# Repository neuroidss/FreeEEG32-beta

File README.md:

# FreeEEG32-beta

### FreeEEG32 Beta, launching soon on [Crowd Supply](https://www.crowdsupply.com/neuroidss/freeeeg32)!

### Setup

Docker container setup (Linux). Extract the following and run:
- Compilation: `./gcc-arm-none-eabi_run.sh`
- Flashing: `sudo ./openocd_flash.sh`

[Flashing via AC6 with STM32 Blue Pill](https://github.com/neuroidss/FreeEEG32-beta/blob/master/SetupGuides/FreeEEG32_Flashing_via_AC6_w_STM32F103_BluePill.md)

The AC6 stuff is deprecated but the blue pill is still needed.

[OpenVIBE Setup](https://github.com/neuroidss/FreeEEG32-beta/blob/master/SetupGuides/FreeEEG32_OpenVibe_Docker_Readme.md)

### Production files
Gerber:   https://github.com/neuroidss/FreeEEG32-beta/blob/master/AssemblyFiles/KiCAD/out/gerber.zip

Assembly: https://github.com/neuroidss/FreeEEG32-beta/blob/master/AssemblyFiles/KiCAD/out/assembly.zip

BOM:      https://github.com/neuroidss/FreeEEG32-beta/blob/master/AssemblyFiles/bom/components%20FreeEEG32%20beta.csv

PCB fabrication constraints:
* Dims: 70mm x 70mm
* Layers: 4
* Thickness: 1.6mm (can vary, thicker = sturdier)
* Surface finish: HASL Lead free or ENIG (more expensive)
* Material: FR4

Assembly constraints:
* Unique parts: 33 (27 without pin headers)
* SMT Pads:  169
* Thruhole: 23 (pin headers only)
* Assembly sides: both

This project is being launched with the help of [HEG Alpha](hegalpha.com) to make science more accessible.
Custom 2 channel and 19 channel headsets are available by Bernard Markus.

### More

Neuroidss home: https://neuroidss.com

[Alpha 1.5 repo with more content and tests](https://github.com/neuroidss/FreeEEG32-alpha1.5)

[BrainFlow support](https://brainflow.readthedocs.io/en/stable/)

[Webapp (WIP)](https://github.com/moothyknight/eegpwa)

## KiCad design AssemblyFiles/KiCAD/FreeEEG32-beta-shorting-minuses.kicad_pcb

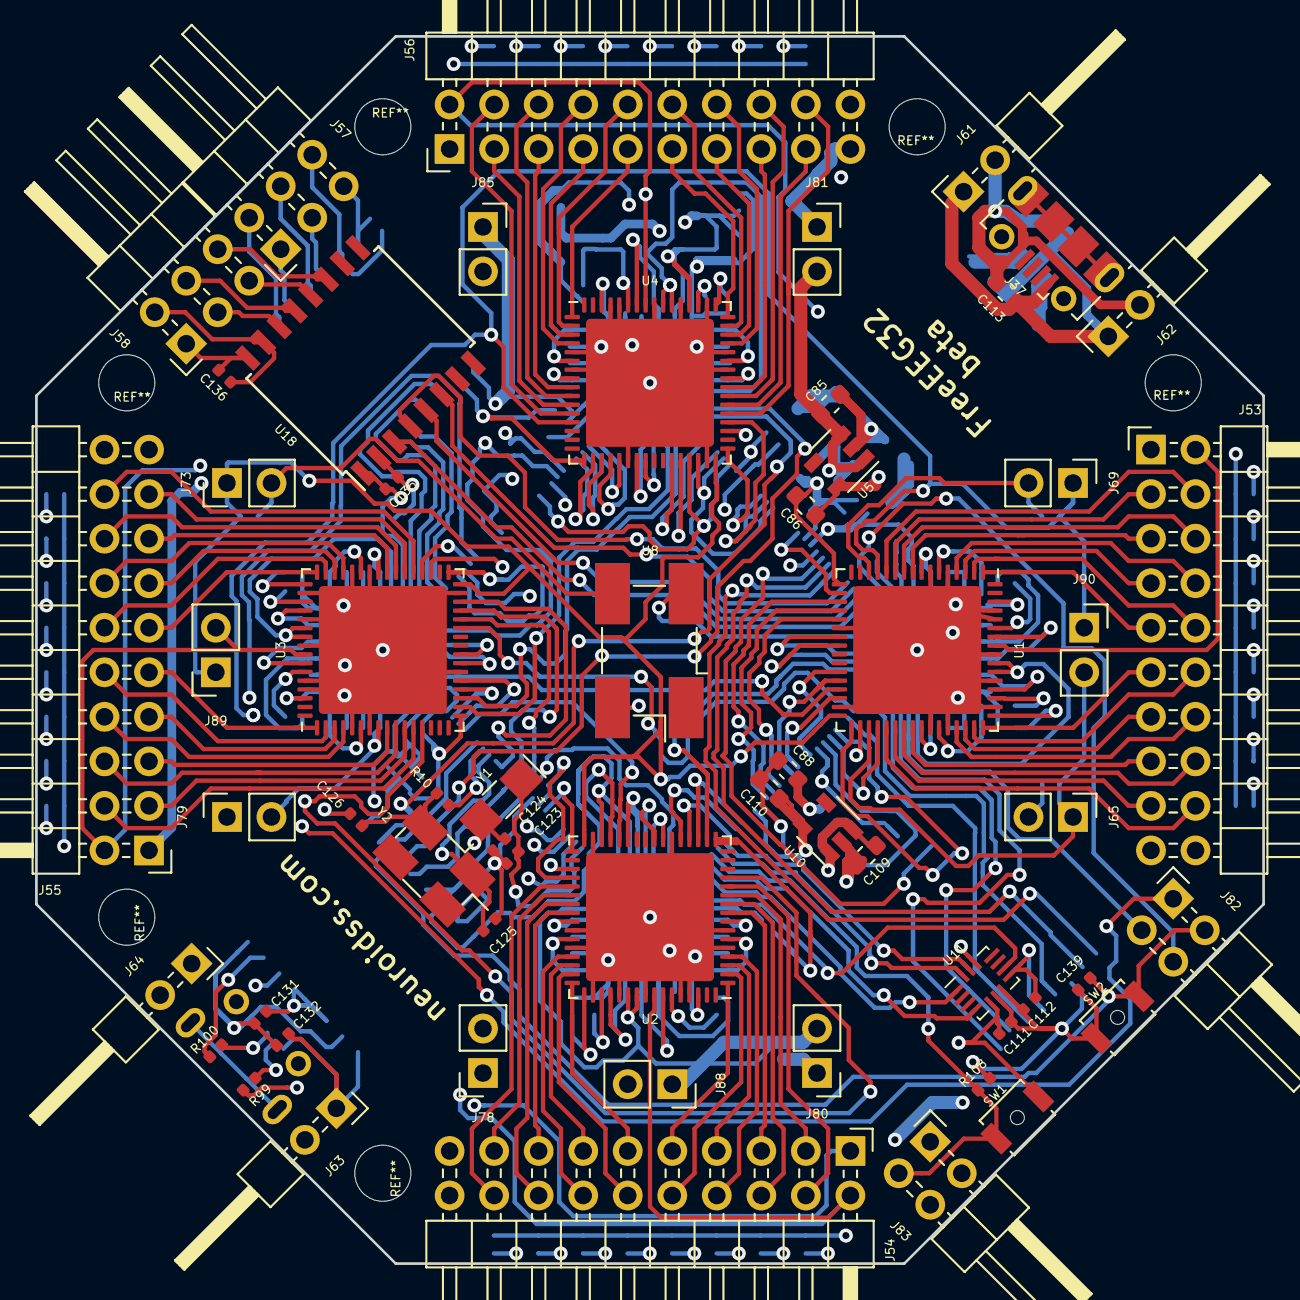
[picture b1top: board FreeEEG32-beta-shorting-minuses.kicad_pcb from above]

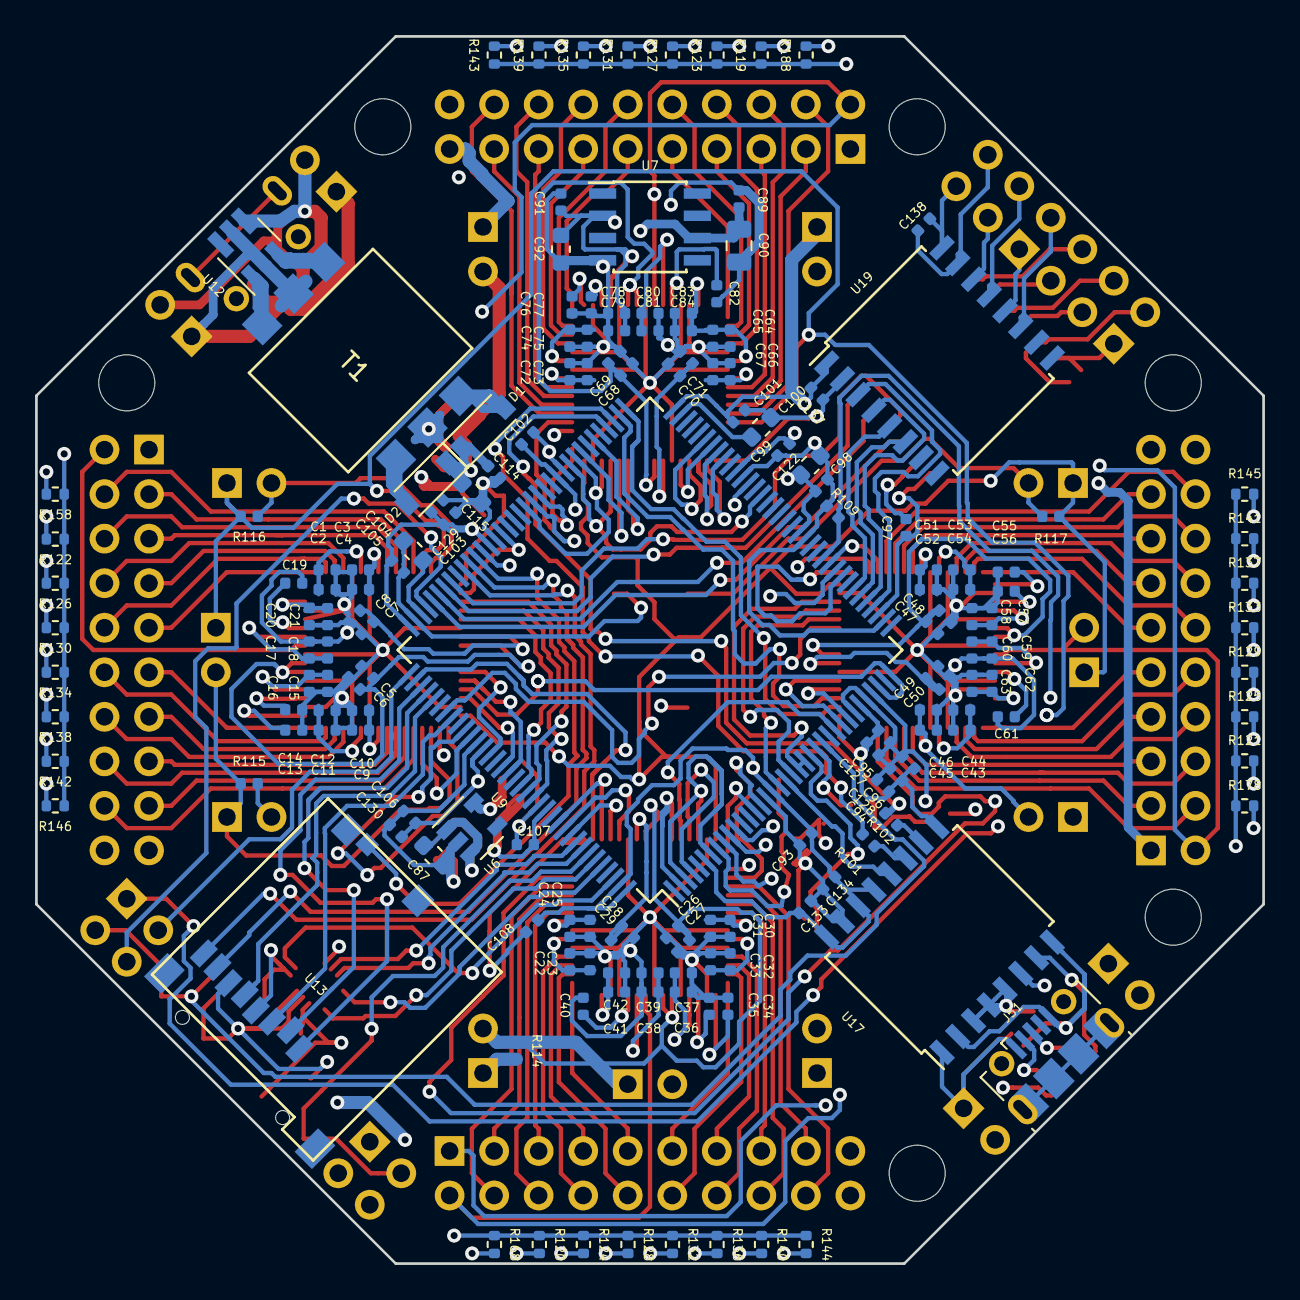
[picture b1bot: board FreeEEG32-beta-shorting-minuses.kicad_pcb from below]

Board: 4 copper layers, 70.0 x 70.0 mm, 224 parts (166 on the bottom side), 195 nets.

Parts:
C1, C3, C5, C7, C9, C11, C13, C14, C15, C17, C19, C20, C22, C24, C26, C28, C30, C32, C34, C35, C36, C38, C40, C41, C43, C45, C47, C49, C51, C53, C55, C56, C57, C59, C61, C62, C64, C66, C68, C70, C72, C74, C76, C77, C78, C80, C82, C83, C89, C91, C93, C94, C95, C96, C97, C98, C99, C101, C102, C103, C105, C106, C107, C108, C111, C112, C114, C131, C132, C133, C134, C135, C136, C137, C138, C139: 100n; C_0402_1005Metric
C2, C4, C6, C8, C10, C12, C16, C18, C21, C23, C25, C27, C29, C31, C33, C37, C39, C42, C44, C46, C48, C50, C52, C54, C58, C60, C63, C65, C67, C69, C71, C73, C75, C79, C81, C84, C127, C128, C129, C130: 1u; C_0402_1005Metric
C85, C86, C87, C88, C100, C104, C109, C110: 2.2u; C_0603_1608Metric
C90: 22u; C_0805_2012Metric
C92, C113, C115: 10u; C_0603_1608Metric
C122: 4.7u; C_0603_1608Metric
C123, C125: CL1; C_0402_1005Metric
C124, C126: CL2; C_0402_1005Metric
D1, D2: D_Schottky; D_SOD-123
J37, J51: USB_B_Micro; USB_Micro-B_Molex-105017-0001
J53, J54, J55, J56: Conn_02x10_Odd_Even; PinHeader_2x10_P2.54mm_Horizontal
J57, J58: Conn_02x03_Odd_Even; PinHeader_2x03_P2.54mm_Horizontal
J61, J62, J63, J64: Conn_01x02; PinHeader_2x01_P2.54mm_Horizontal
J65, J69, J73, J80: Conn_01x02; PinHeader_1x02_P2.54mm_Vertical
J78, J79, J81, J85, J88, J89, J90: Conn_01x02; PinSocket_1x02_P2.54mm_Vertical
J82, J83: Conn_02x02_Odd_Even; PinHeader_2x02_P2.54mm_Horizontal
R10: R_EXT; R_0402_1005Metric
R99, R100, R101, R102: 24; R_0402_1005Metric
R108, R109: 4k7; R_0402_1005Metric
R114, R115, R116, R117, R119, R120, R121, R122, R123, R124, R125, R126, R127, R128, R129, R130, R131, R132, R133, R134, R135, R136, R137, R138, R139, R140, R141, R142, R143, R144, R145, R146, R158, R168, R178, R188: 0; R_0402_1005Metric
SW1, SW2: SW_Push; SW_SPST_B3U-1000P-B
T1: 750315371
U1, U2, U3, U4: AD7779; QFN-64-1EP_9x9mm_P0.5mm_EP7.3x7.3mm
U5, U6, U10: LP5907; SOT-23-5
U7: ADR4525; SOIC-8_3.9x4.9mm_P1.27mm
U8: FXO-SM7_OSC-SMD7050_short; Oscillator_SMD_EuroQuartz_XO91-4Pin_7.0x5.0mm_HandSoldering
U9: STM32H743ZITx; LQFP-144_20x20mm_P0.5mm
U11: LSM6DS3; Bosch_LGA-14_3x2.5mm_P0.5mm
U12: SN6505B; SOT-23-6_Handsoldering
U13: 473521001
U17: ADuM3160; SOIC-16W_7.5x10.3mm_P1.27mm
U18: ADUM1402BRWZ; SOIC-16W_7.5x10.3mm_P1.27mm
U19: ISO7341c; SOIC-16W_7.5x10.3mm_P1.27mm
Y1: 32768Hz; Crystal_SMD_EuroQuartz_EQ161-2Pin_3.2x1.5mm_HandSoldering
Y2: 16MHz; Crystal_SMD_EuroQuartz_MJ-4Pin_5.0x3.2mm_HandSoldering

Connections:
/ADC1/1_AIN0-: J53.9, R130.2, U1.1 (AIN0-)
/ADC1/2_AIN0+: J53.10, U1.2 (AIN0+)
/ADC1/3_AIN1-: J53.7, R126.2, U1.3 (AIN1-)
/ADC1/4_AIN1+: J53.8, U1.4 (AIN1+)
/ADC1/9_AIN2-: J53.5, R122.2, U1.9 (AIN2-)
/ADC1/10_AIN2+: J53.6, U1.10 (AIN2+)
/ADC1/11_AIN3-: J53.3, R158.2, U1.11 (AIN3-)
/ADC1/12_AIN3+: J53.4, U1.12 (AIN3+)
/ADC1/37_AIN7+: J53.18, U1.37 (AIN7+)
/ADC1/38_AIN7-: J53.17, R146.2, U1.38 (AIN7-)
/ADC1/39_AIN6+: J53.16, U1.39 (AIN6+)
/ADC1/40_AIN6-: J53.15, R142.2, U1.40 (AIN6-)
/ADC1/45_AIN5+: J53.14, U1.45 (AIN5+)
/ADC1/46_AIN5-: J53.13, R138.2, U1.46 (AIN5-)
/ADC1/47_AIN4+: J53.12, U1.47 (AIN4+)
/ADC1/48_AIN4-: J53.11, R134.2, U1.48 (AIN4-)
/ADC1/49_REF_OUT: C13.1, U1.49 (REF_OUT)
/ADC1/51_AREG2CAP: C14.1, U1.51 (AREG2CAP)
/ADC1/59_AREG1CAP: C19.1, U1.59 (AREG1CAP)
/ADC2/1_AIN0-: J54.9, R128.2, U2.1 (AIN0-)
/ADC2/2_AIN0+: J54.10, U2.2 (AIN0+)
/ADC2/3_AIN1-: J54.7, R124.2, U2.3 (AIN1-)
/ADC2/4_AIN1+: J54.8, U2.4 (AIN1+)
/ADC2/9_AIN2-: J54.5, R120.2, U2.9 (AIN2-)
/ADC2/10_AIN2+: J54.6, U2.10 (AIN2+)
/ADC2/11_AIN3-: J54.3, R168.2, U2.11 (AIN3-)
/ADC2/12_AIN3+: J54.4, U2.12 (AIN3+)
/ADC2/37_AIN7+: J54.18, U2.37 (AIN7+)
/ADC2/38_AIN7-: J54.17, R144.2, U2.38 (AIN7-)
/ADC2/39_AIN6+: J54.16, U2.39 (AIN6+)
/ADC2/40_AIN6-: J54.15, R140.2, U2.40 (AIN6-)
/ADC2/45_AIN5+: J54.14, U2.45 (AIN5+)
/ADC2/46_AIN5-: J54.13, R136.2, U2.46 (AIN5-)
/ADC2/47_AIN4+: J54.12, U2.47 (AIN4+)
/ADC2/48_AIN4-: J54.11, R132.2, U2.48 (AIN4-)
/ADC2/49_REF_OUT: C34.1, U2.49 (REF_OUT)
/ADC2/51_AREG2CAP: C35.1, U2.51 (AREG2CAP)
/ADC2/59_AREG1CAP: C40.1, U2.59 (AREG1CAP)
/ADC3/1_AIN0-: J55.9, R129.2, U3.1 (AIN0-)
/ADC3/2_AIN0+: J55.10, U3.2 (AIN0+)
/ADC3/3_AIN1-: J55.7, R125.2, U3.3 (AIN1-)
/ADC3/4_AIN1+: J55.8, U3.4 (AIN1+)
/ADC3/9_AIN2-: J55.5, R121.2, U3.9 (AIN2-)
/ADC3/10_AIN2+: J55.6, U3.10 (AIN2+)
/ADC3/11_AIN3-: J55.3, R178.2, U3.11 (AIN3-)
/ADC3/12_AIN3+: J55.4, U3.12 (AIN3+)
/ADC3/37_AIN7+: J55.18, U3.37 (AIN7+)
/ADC3/38_AIN7-: J55.17, R145.2, U3.38 (AIN7-)
/ADC3/39_AIN6+: J55.16, U3.39 (AIN6+)
/ADC3/40_AIN6-: J55.15, R141.2, U3.40 (AIN6-)
/ADC3/45_AIN5+: J55.14, U3.45 (AIN5+)
/ADC3/46_AIN5-: J55.13, R137.2, U3.46 (AIN5-)
/ADC3/47_AIN4+: J55.12, U3.47 (AIN4+)
/ADC3/48_AIN4-: J55.11, R133.2, U3.48 (AIN4-)
/ADC3/49_REF_OUT: C55.1, U3.49 (REF_OUT)
/ADC3/51_AREG2CAP: C56.1, U3.51 (AREG2CAP)
/ADC3/59_AREG1CAP: C61.1, U3.59 (AREG1CAP)
/ADC4/37_AIN7+: J56.18, U4.37 (AIN7+)
/ADC4/38_AIN7-: J56.17, R143.2, U4.38 (AIN7-)
/ADC4/39_AIN6+: J56.16, U4.39 (AIN6+)
/ADC4/40_AIN6-: J56.15, R139.2, U4.40 (AIN6-)
/ADC4/45_AIN5+: J56.14, U4.45 (AIN5+)
/ADC4/46_AIN5-: J56.13, R135.2, U4.46 (AIN5-)
/ADC4/47_AIN4+: J56.12, U4.47 (AIN4+)
/ADC4/48_AIN4-: J56.11, R131.2, U4.48 (AIN4-)
/ADC4/49_REF_OUT: C76.1, U4.49 (REF_OUT)
/ADC4/51_AREG2CAP: C77.1, U4.51 (AREG2CAP)
/ADC4/59_AREG1CAP: C82.1, U4.59 (AREG1CAP)
/MCU/8_PC14: C123.1, U9.8 (PC14), Y1.1
/MCU/9_PC15: C124.1, U9.9 (PC15), Y1.2
/MCU/23_PH0: C125.1, U9.88 (PG3), Y2.1
/MCU/24_PH1: R10.1, U9.89 (PG4)
/MCU/106_VCAP_2: C104.1, U9.143 (PDR_ON)
ACC_1_SDO_SAO: U9.140 (PB9), U11.1 (SDO/SA0)
ACC_4_INT1: U9.139 (PB8), U11.4 (INT1)
ACC_9_INT2: U9.58 (PE7), U11.9 (INT2)
ACC_12_CS: C93.1, C94.1, C95.1, C96.1, C97.1, C98.1, C99.1, C101.1, C102.1, C103.1, C105.1, C106.1, C107.1, C108.1, C110.1, C111.1, C112.1, C122.1, C127.1, C128.1, C129.1, C130.1, C133.1, C134.1, C135.1, C137.1, J83.1, J85.1, SW1.1, U9.6 (VBAT), U9.17 (VDD), U9.30 (VDD), U9.39 (VDD), U9.52 (VDD), U9.62 (VDD), U9.72 (VDD), U9.84 (VDD), U9.95 (VDD33_USB), U9.108 (VDD), U9.121 (VDD), U9.131 (VDD), U9.144 (VDD), U10.5 (OUT), U11.5 (VDDIO), U11.8 (VDD), U11.12 (CS), U13.4 (VDD), U17.13 (SPD), U17.14 (VDD2), U17.16 (VBUS2), U18.1 (VCC1), U19.1 (VCC1)
ACC_13_SCL: U9.136 (PB6), U11.13 (SCL)
ACC_14_SDA: U9.137 (PB7), U11.14 (SDA)
ADC1_13_MODE0_GPIO0: J69.1, J90.1, R116.2, U1.13 (MODE0/GPIO0), U2.13 (MODE0/GPIO0), U3.13 (MODE0/GPIO0), U4.13 (MODE0/GPIO0)
ADC1_14_MODE1_GPIO1: J69.2, R116.1, U1.14 (MODE1/GPIO1)
ADC1_18_ALERT_CS: U1.18 (ALERT/CS), U9.129 (PG14)
ADC1_19_DCLK2_SCLK: U1.19 (DCLK2/SCLK), U9.12 (PF2)
ADC1_20_DCLK1_SDI: U1.20 (DCLK1/SDI), U9.13 (PF3)
ADC1_21_DCLK0_SDO: U1.21 (DCLK0/SDO), U9.11 (PF1)
ADC1_23_DREGCAP: C7.2, C8.2, U1.23 (DREGCAP)
ADC1_24_IOVDD: C5.2, C6.2, C26.2, C27.2, C47.2, C48.2, C68.2, C69.2, C88.1, J80.2, J88.1, R114.1, U1.24 (IOVDD), U1.54 (FORMAT1), U1.55 (FORMAT0), U2.24 (IOVDD), U2.54 (FORMAT1), U2.55 (FORMAT0), U3.24 (IOVDD), U3.54 (FORMAT1), U3.55 (FORMAT0), U4.24 (IOVDD), U4.54 (FORMAT1), U4.55 (FORMAT0), U6.5 (OUT)
ADC1_27_DOUT1: U1.27 (DOUT1), U9.122 (PD6)
ADC1_29_DCLK: U1.29 (DCLK), U9.34 (PA0), U9.36 (PA2)
ADC1_30_DRDY: U1.30 (DRDY), U9.46 (PB0), U9.96 (PC6), U9.132 (PG15)
ADC1_32_XTAL2_MCLK: J73.1, J89.1, R117.2, U1.32 (XTAL2/MCLK), U2.32 (XTAL2/MCLK), U3.32 (XTAL2/MCLK), U4.32 (XTAL2/MCLK)
ADC1_33_START: U1.33 (START), U9.118 (PD4)
ADC1_34_SYNC_OUT: J65.2, R115.1, U1.34 (SYNC_OUT)
ADC1_35_SYNC_IN: J65.1, J90.2, R115.2, U1.35 (SYNC_IN), U2.35 (SYNC_IN), U3.35 (SYNC_IN), U4.35 (SYNC_IN)
ADC1_36_RESET: U1.36 (RESET), U9.119 (PD5)
ADC1_41_REF2+: C3.2, C4.2, C9.2, C10.2, C24.2, C25.2, C30.2, C31.2, C45.2, C46.2, C51.2, C52.2, C66.2, C67.2, C72.2, C73.2, C89.1, C90.1, J79.2, U1.8 (REF1+), U1.41 (REF2+), U2.8 (REF1+), U2.41 (REF2+), U3.8 (REF1+), U3.41 (REF2+), U4.8 (REF1+), U4.41 (REF2+), U7.6 (VOUT)
ADC1_43_AVDD1B: C1.2, C2.2, C11.2, C12.2, C15.2, C16.2, C17.2, C18.2, C20.1, C21.1, C22.2, C23.2, C32.2, C33.2, C36.2, C37.2, C38.2, C39.2, C41.1, C42.1, C43.2, C44.2, C53.2, C54.2, C57.2, C58.2, C59.2, C60.2, C62.1, C63.1, C64.2, C65.2, C74.2, C75.2, C78.2, C79.2, C80.2, C81.2, C83.1, C84.1, C86.1, C91.1, C92.1, J53.20, J54.20, J55.20, J56.20, J85.2, U1.6 (AVDD1A), U1.43 (AVDD1B), U1.52 (AVDD2B), U1.58 (AVDD2A), U1.62 (AVDD4), U2.6 (AVDD1A), U2.43 (AVDD1B), U2.52 (AVDD2B), U2.58 (AVDD2A), U2.62 (AVDD4), U3.6 (AVDD1A), U3.43 (AVDD1B), U3.52 (AVDD2B), U3.58 (AVDD2A), U3.62 (AVDD4), U4.6 (AVDD1A), U4.43 (AVDD1B), U4.52 (AVDD2B), U4.58 (AVDD2A), U4.62 (AVDD4), U5.5 (OUT), U7.2 (VIN)
ADC1_57_VCM: J53.2, J54.2, J55.2, J56.2, J89.2, U1.57 (VCM), U2.57 (VCM), U3.57 (VCM), U4.57 (VCM)
ADC2_18_ALERT_CS: U2.18 (ALERT/CS), U9.110 (PA15)
ADC2_19_DCLK2_SCLK: U2.19 (DCLK2/SCLK), U9.133 (PB3)
ADC2_20_DCLK1_SDI: U2.20 (DCLK1/SDI), U9.135 (PB5)
ADC2_21_DCLK0_SDO: U2.21 (DCLK0/SDO), U9.134 (PB4)
ADC2_23_DREGCAP: C28.2, C29.2, U2.23 (DREGCAP)
ADC2_27_DOUT1: U2.27 (DOUT1), U9.60 (PE9)
ADC2_28_DOUT0: U2.28 (DOUT0), U9.27 (PC1)
ADC2_29_DCLK: U2.29 (DCLK), U9.64 (PE11)
ADC2_30_DRDY: U2.30 (DRDY), U9.7 (PC13), U9.63 (PE10)
ADC2_33_START: U2.33 (START), U9.22 (PF10)
ADC2_36_RESET: U2.36 (RESET), U9.49 (PF11)
ADC3_18_ALERT_CS: U3.18 (ALERT/CS), U9.73 (PB12)
ADC3_19_DCLK2_SCLK: U3.19 (DCLK2/SCLK), U9.74 (PB13)
ADC3_20_DCLK1_SDI: U3.20 (DCLK1/SDI), U9.29 (PC3_C)
ADC3_21_DCLK0_SDO: U3.21 (DCLK0/SDO), U9.28 (PC2_C)
ADC3_23_DREGCAP: C49.2, C50.2, U3.23 (DREGCAP)
ADC3_27_DOUT1: U3.27 (DOUT1), U9.115 (PD1)
ADC3_28_DOUT0: U3.28 (DOUT0), U9.50 (PF12)
ADC3_29_DCLK: U3.29 (DCLK), U9.54 (PF14)
ADC3_30_DRDY: U3.30 (DRDY), U9.55 (PF15)
ADC3_33_START: U3.33 (START), U9.45 (PC5)
ADC3_36_RESET: U3.36 (RESET), U9.47 (PB1)
ADC4_18_ALERT_CS: U4.18 (ALERT/CS), U9.71 (VCAP)
ADC4_19_DCLK2_SCLK: U4.19 (DCLK2/SCLK), U9.106 (VCAP)
ADC4_23_DREGCAP: C70.2, C71.2, U4.23 (DREGCAP)
ADC4_27_DOUT1: U4.27 (DOUT1), U9.78 (PD9)
ADC4_28_DOUT0: U4.28 (DOUT0), U9.80 (PD11)
ADC4_29_DCLK: U4.29 (DCLK), U9.66 (PE13), U9.82 (PD13)
ADC4_30_DRDY: U4.30 (DRDY), U9.68 (PE15), U9.81 (PD12), U9.125 (PG10)
ADC4_33_START: U4.33 (START), U9.93 (PG8)
ADC4_36_RESET: U4.36 (RESET), U9.124 (PG9)
ADC4_AIN0+: J56.10, U4.2 (AIN0+)
ADC4_AIN0-: J56.9, R127.2, U4.1 (AIN0-)
ADC4_AIN1+: J56.8, U4.4 (AIN1+)
ADC4_AIN1-: J56.7, R123.2, U4.3 (AIN1-)
ADC4_AIN2+: J56.6, U4.10 (AIN2+)
ADC4_AIN2-: J56.5, R119.2, U4.9 (AIN2-)
ADC4_AIN3+: J56.4, U4.12 (AIN3+)
ADC4_AIN3-: J56.3, R188.2, U4.11 (AIN3-)
AINREF-: J53.1, J54.1, J55.1, J56.1, J88.2, R119.1, R120.1, R121.1, R122.1, R123.1, R124.1, R125.1, R126.1, R127.1, R128.1, R129.1, R130.1, R131.1, R132.1, R133.1, R134.1, R135.1, R136.1, R137.1, R138.1, R139.1, R140.1, R141.1, R142.1, R143.1, R144.1, R145.1, R146.1, R158.1, R168.1, R178.1, R188.1
AVDD_1_IN: C85.1, C87.1, C109.1, C114.1, C115.1, D1.1 (K), D2.1 (K), J81.2, J83.4, U5.1 (IN), U5.3 (EN), U6.1 (IN), U6.3 (EN), U10.1 (IN), U10.3 (EN)
CRYSTAL_3_OUT: J73.2, R117.1, U8.3 (OUT)
CRYSTAL_4_Vin: J80.1, R114.2, U8.4 (Vin)
ISO_SPI_3_INA: U9.40 (PA4), U19.3 (INA)
ISO_SPI_4_INB: U9.41 (PA5), U19.4 (INB)
ISO_SPI_5_INC: U9.43 (PA7), U19.5 (INC)
ISO_SPI_6_OUTD: U9.42 (PA6), U19.6 (OUTD)
ISO_SPI_11_IND: J57.2, U19.11 (IND)
ISO_SPI_12_OUTC: J57.1, U19.12 (OUTC)
ISO_SPI_13_OUTB: J57.4, U19.13 (OUTB)
ISO_SPI_14_OUTA: J57.3, U19.14 (OUTA)
ISO_SPI_15_GND2: C138.2, J57.6, U19.15 (GND2)
ISO_SPI_16_VCC2: C138.1, J57.5, U19.16 (VCC2)
ISO_UART_3_INA: U9.104 (PA12), U18.3 (INA)
ISO_UART_4_INB: U9.101 (PA9), U18.4 (INB)
ISO_UART_5_OUTC: U9.103 (PA11), U18.5 (OUTC)
ISO_UART_6_OUTD: U9.102 (PA10), U18.6 (OUTD)
ISO_UART_11_IND: J58.6, U18.11 (IND)
ISO_UART_12_INC: J58.5, U18.12 (INC)
ISO_UART_13_OUTB: J58.4, U18.13 (OUTB)
ISO_UART_14_OUTA: J58.3, U18.14 (OUTA)
ISO_UART_15_GND2: C136.2, J58.2, U18.15 (GND2)
ISO_UART_16_VCC2: C136.1, J58.1, U18.16 (VCC2)
ISO_USB_1_VBUS1: C132.1, J51.1 (VBUS), J63.1, U17.1 (VBUS1)
ISO_USB_3_VDD1: C131.1, U17.3 (VDD1), U17.4 (PDEN), U17.5 (SPU)
ISO_USB_6_UD–: J51.2 (D-), J64.2, R99.2
ISO_USB_7_UD+: J51.3 (D+), J64.1, R100.2
ISO_USB_8_GND1: C131.2, C132.2, J51.5 (GND), J63.2, U17.2 (GND1), U17.8 (GND1)
ISO_USB_10_DD+: R102.1, U9.76 (PB15)
ISO_USB_11_DD–: R101.1, U9.75 (PB14)
ISO_USB_12_PIN: U9.53 (PF13), U17.12 (PIN)
MCU_10_PF0_I2C2_SDA: J78.2, U9.18 (PF6)
MCU_11_PF1_I2C2_SCL: J78.1, U9.19 (PF7)
MCU_25_NRST: C139.2, J82.2, SW2.2, U9.25 (NRST)
MCU_48_PB2_BOOT1: J82.1, R109.1, U9.48 (PB2)
MCU_51_VSS: C1.1, C2.1, C3.1, C4.1, C5.1, C6.1, C7.1, C8.1, C9.1, C10.1, C11.1, C12.1, C13.2, C14.2, C15.1, C16.1, C17.1, C18.1, C19.2, C20.2, C21.2, C22.1, C23.1, C24.1, C25.1, C26.1, C27.1, C28.1, C29.1, C30.1, C31.1, C32.1, C33.1, C34.2, C35.2, C36.1, C37.1, C38.1, C39.1, C40.2, C41.2, C42.2, C43.1, C44.1, C45.1, C46.1, C47.1, C48.1, C49.1, C50.1, C51.1, C52.1, C53.1, C54.1, C55.2, C56.2, C57.1, C58.1, C59.1, C60.1, C61.2, C62.2, C63.2, C64.1, C65.1, C66.1, C67.1, C68.1, C69.1, C70.1, C71.1, C72.1, C73.1, C74.1, C75.1, C76.2, C77.2, C78.1, C79.1, C80.1, C81.1, C82.2, C83.2, C84.2, C85.2, C86.2, C87.2, C88.2, C89.2, C90.2, C91.2, C92.2, C93.2, C94.2, C95.2, C96.2, C97.2, C98.2, C99.2, C100.2, C101.2, C102.2, C103.2, C104.2, C105.2, C106.2, C107.2, C108.2, C109.2, C110.2, C111.2, C112.2, C114.2, C115.2, C122.2, C123.2, C124.2, C125.2, C126.2, C127.2, C128.2, C129.2, C130.2, C133.2, C134.2, C135.2, C137.2, C139.1, J53.19, J54.19, J55.19, J56.19, J79.1, J81.1, J83.2, R108.2, R109.2, SW2.1, T1.5, U1.5 (AVSS1A), U1.7 (REF1-), U1.17 (CONVST_SAR), U1.22 (DGND), U1.31 (XTAL1), U1.42 (REF2-), U1.44 (AVSS1B), U1.50 (AVSS2B), U1.53 (AVSS3), U1.56 (CLK_SEL), U1.60 (AVSS2A), U1.61 (AVSS4), U1.65 (EPAD), U2.5 (AVSS1A), U2.7 (REF1-), U2.17 (CONVST_SAR), U2.22 (DGND), U2.31 (XTAL1), U2.42 (REF2-), U2.44 (AVSS1B), U2.50 (AVSS2B), U2.53 (AVSS3), U2.56 (CLK_SEL), U2.60 (AVSS2A), U2.61 (AVSS4), U2.65 (EPAD), U3.5 (AVSS1A), U3.7 (REF1-), U3.17 (CONVST_SAR), U3.22 (DGND), U3.31 (XTAL1), U3.42 (REF2-), U3.44 (AVSS1B), U3.50 (AVSS2B), U3.53 (AVSS3), U3.56 (CLK_SEL), U3.60 (AVSS2A), U3.61 (AVSS4), U3.65 (EPAD), U4.5 (AVSS1A), U4.7 (REF1-), U4.17 (CONVST_SAR), U4.22 (DGND), U4.31 (XTAL1), U4.42 (REF2-), U4.44 (AVSS1B), U4.50 (AVSS2B), U4.53 (AVSS3), U4.56 (CLK_SEL), U4.60 (AVSS2A), U4.61 (AVSS4), U4.65 (EPAD), U5.2 (GND), U6.2 (GND), U7.4 (GND), U8.2 (GND), U9.16 (VSS), U9.31 (VSSA), U9.38 (VSS), U9.51 (VSS), U9.61 (VSS), U9.83 (VSS), U9.94 (VSS), U9.107 (VSS), U9.120 (VSS), U9.130 (VSS), U10.2 (GND), U11.6 (GND), U11.7 (GND), U13.6 (Vss), U17.9 (GND2), U17.15 (GND2), U18.2 (GND1), U19.2 (GND1)
MCU_97_PC7_SDMMC1_DETECT: U9.97 (PC7), U13.9 (DETECT)
MCU_98_PC8_SDMMC1_D0: U9.98 (PC8), U13.7 (DATA0)
MCU_99_PC9_SDMMC1_D1: U9.99 (PC9), U13.8 (DATA1)
MCU_105_PA13_SYS_JTMS-SWDIO: J82.4, U9.105 (PA13)
MCU_109_PA14_SYS_JTCK-SWCLK: J82.3, U9.109 (PA14)
MCU_111_PC10_SDMMC1_D2: U9.111 (PC10), U13.1 (DATA2)
MCU_112_PC11_SDMMC1_D3: U9.112 (PC11), U13.2 (DATA3)
MCU_113_PC12_SDMMC1_CK: U9.113 (PC12), U13.5 (CLK)
MCU_116_PD2_SDMMC1_CMD: U9.116 (PD2), U13.3 (CMD)
MCU_138_BOOT0: J83.3, R108.1, SW1.2
unnamed: C126.1, R10.2, Y2.2
unnamed: D1.2 (A), T1.6
unnamed: D2.2 (A), T1.4
unnamed: T1.3, U12.1 (D1)
unnamed: T1.1, U12.3 (D2)
unnamed: R102.2, U17.10 (DD+)
unnamed: R101.2, U17.11 (DD–)
unnamed: R100.1, U17.7 (UD+)
unnamed: R99.1, U17.6 (UD–)
POWER_1_GND: C113.1, J37.5 (GND), J61.2, J62.2, U12.4 (GND)
POWER_2_VCC: C113.2, J37.1 (VBUS), J61.1, J62.1, T1.2, U12.2 (VCC), U12.5 (EN)
